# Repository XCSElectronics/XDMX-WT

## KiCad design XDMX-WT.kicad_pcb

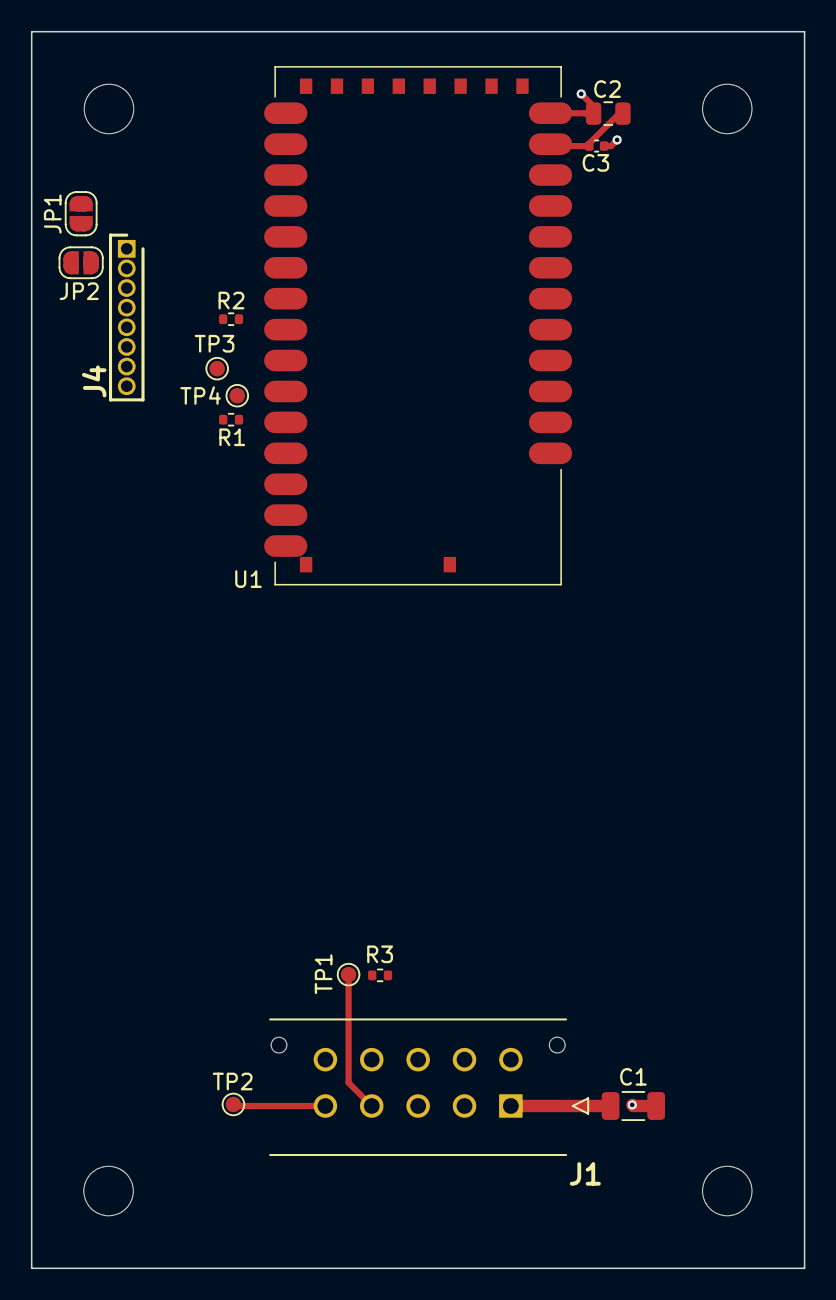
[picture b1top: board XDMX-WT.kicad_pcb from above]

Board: 2 copper layers, 50.0 x 80.0 mm, 15 parts (0 on the bottom side), 16 nets.

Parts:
C1: 22uF; C_1206_3216Metric
C2: 10uF; C_0805_2012Metric
C3: 100nF; C_0402_1005Metric
J1: 43045-1012; 43045-10YY_121314
J4: M50-3530842; HDRV8W40P0X127_1X8_1016X210X400P
JP1, JP2: Jumper_2_Bridged; SolderJumper-2_P1.3mm_Open_RoundedPad1.0x1.5mm
R1, R2: 33R; R_0402_1005Metric
R3: 1k; R_0402_1005Metric
TP1, TP2, TP3, TP4: TestPoint; TestPoint_Pad_D1.0mm
U1: TIMO_TWO_MODULE; TimoTwo Module

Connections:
3V3_LIGHTS: C1.1, C2.1, C3.1, J1.1, U1.P36 (VDD)
CS: J4.4, JP1.2 (B), U1.P3 (C.S.)
DMX_DE: J1.4, TP1.1 (1_1)
DMX_EN_FLT: J1.9, R3.1
DMX_NRE: J1.5, TP2.1 (1_1)
GND: C1.2, C2.2, C3.2, J1.6, J1.7, J1.8, J1.10, J4.2, J4.8, JP2.2 (B), U1.P1 (VSS), U1.P7 (VSS), U1.P9 (VSS), U1.P22 (VSS), U1.P23 (VSS), U1.P24 (VSS), U1.P25 (VSS), U1.P26 (VSS), U1.P27 (VSS), U1.P30 (VSS), U1.P37 (VSS)
IRQ: J4.3, JP1.1 (A), U1.P2 (IRQ)
MISO: J4.7, U1.P6 (MISO)
MOSI: J4.6, JP2.1 (A), U1.P5 (MOSI)
unnamed: J1.2, R2.2
unnamed: J1.3, R1.2
RF_LINK: R3.2, U1.P35 (RF_LINK)
RS485_DE: TP3.1 (1_1), U1.P10 (RS485_DE)
RS485_RE: TP4.1 (1_1), U1.P11 (RS485_RE)
SCK: J4.5, U1.P4 (SCK)
U1_DMX_TXD: R1.1, R2.1, U1.P8 (DMX_TXD)
